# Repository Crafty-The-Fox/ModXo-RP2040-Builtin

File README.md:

# ModXo-RP2040-Included-Edition

A carrier board for the ModXo V1.0 with added support for Epimetheus. Based off of Darkone83's work. (reversed from gerbers and provided documents on the github page)

NOTE: anything after this is from the other repo.

This is designed around Team Resutgent's and Shalx's work on ModXo an open-source modchip, with additional support for OfficialTeamUIX's Epimetheus incorporated into the PCB

Mouser Cart: <a href="https://www.mouser.com/ProjectManager/ProjectDetail.aspx?AccessID=a62729557a">Here</a>

RP2040 Tiny: <a href="https://www.aliexpress.us/item/3256805837992528.html?spm=a2g0o.productlist.main.21.2f7926c5zGZBOW&algo_pvid=a59806cb-1f8b-4000-8595-0b05ca9fd6e6&algo_exp_id=a59806cb-1f8b-4000-8595-0b05ca9fd6e6-10&pdp_npi=4%40dis%21USD%217.22%214.48%21%21%217.22%214.48%21%402101c80217323295821625728e786b%2112000035369681956%21sea%21US%21196794698%21X&curPageLogUid=5ESoEvR4Kxce&utparam-url=scene%3Asearch%7Cquery_from%3A">AliExpress</a>, <a href="https://www.amazon.com/gp/product/B0CHDW1MY5/ref=ppx_yo_dt_b_asin_title_o02_s00?ie=UTF8&psc=1">Amazon</a>

JST SH 6 Pin Cables: 

<a href="https://www.aliexpress.us/item/3256804332710255.html?spm=a2g0o.detail.pcDetailTopMoreOtherSeller.5.245bNc4KNc4Kdm&gps-id=pcDetailTopMoreOtherSeller&scm=1007.40050.354490.0&scm_id=1007.40050.354490.0&scm-url=1007.40050.354490.0&pvid=6b58b5af-718a-4929-bfb1-9a0c24fd9d3c&_t=gps-id:pcDetailTopMoreOtherSeller,scm-url:1007.40050.354490.0,pvid:6b58b5af-718a-4929-bfb1-9a0c24fd9d3c,tpp_buckets:668%232846%238112%231997&pdp_npi=4%40dis%21USD%210.46%210.40%21%21%210.46%210.40%21%402103241117302619299196939e5dfc%2112000029449896682%21rec%21US%21196794698%21X&utparam-url=scene%3ApcDetailTopMoreOtherSeller%7Cquery_from%3A">AliExpress</a> Select 100mm length, 6 Pin 10 Pcs, SH 1.0MM Dual for Color, Request same direction!!!

Or if you want to build out your own you can use this listing on <a href="https://www.amazon.com/gp/product/B0BKSNMCV4/ref=ppx_yo_dt_b_asin_title_o03_s00?ie=UTF8&psc=1">Amazon</a>

For more information on the software side of things and the ModXo project please visit: https://github.com/Team-Resurgent/Modxo

For more information on Epimetheus please visit: https://github.com/OfficialTeamUIX/Epimetheus 

### Notice

No firmware is provided for the STM32 you will need to either code your own firmware or legally obtain a firmware image

#### Builder's note

If your XBOX is a revision 1.6 you will need to rebuild the LPC manually or use a LPC rebuild PCB.

# Purchase

Fully assembled boards and PCB's can be purchased via <a href="https://darkonecustoms.com">Darkone Customs</a>

PCB Only: <a href="https://www.darkonecustoms.com/store/p/modxo-epimetheus-pcb">Here</a>

Fully Assembled Board: <a href="https://www.darkonecustoms.com/store/p/modxo-epimetheus-fully-assembled">Here</a> *Fully assembled boards do not contain any firmware for the STM32*

# Navigation

Both the Bom and iBOMS are located in the root folder. iBOMS are included for the full-size board and the new Smol revision, Large board has been moved to archive

Archive: Will contain older functional gerbers and pick and place files as the board revs, along with older board images and older iBOMS.

Images: Contains branding images along with PCB images for the full-size and the Smol board, the schematic is also included here and is the same for both boards along with images of the various header pinouts and soldering locations

Smol: Contains gerbers for the Smol board along with the pick-and-place file

# Assembly

### ModXo

It's recommended to assemble the ModXo potion of the board first and test it. These parts include U1, D1, LED2, R1-4, R6, and the LPC headder. After functionality has been confirmed move on to the VCC circuit assembly

### VCC circuit

The VCC Circuit pulls 5V and GND from the LPC 5V on the 5V pad and GND can be found on PINs 2,12. The VCC circuit consists of the following parts U5, L1, C1-C2. After assembly, you can test PIN 5 of U5 to ensure a stable 3.3V output. Once you have confirmed you have 3.3V continue to assemble the STM32 circuit

### STM32

The STM32F030C8C6 is the core of the Epimetheus functionality portion of the board these components include U2. R7-10, C3-C6. Do not install R9 until you have programmed your STM32. Once assembly is complete you can proceed to program your STM32 Review the NRST Harness diagram and temporarily install it for programming. The NRST wire will connect to the top pad of R9 (the one closest to the MCU) and the GND side to any viable GND source. Remove the NRST harness once you have verified and tested your firmware. Install R9 to complete the STM32 circuit. SDA is pulled directly from PIN 13 of the LPC header and SCL is pulled directly from PIN 14. Pinouts will be listed below. Proceed to Port assembly

#### STM32 PWR and Enable
Attach a +5V source to the 5V pad on the topside of the board. On the back of the board jumper, both boxes are labeled enable with a solder blob. This was designed this way to assist in isolating the STM32 and the ModXo. As a quick tap, you can pull +5V from the bottom of LED2. 

### Port Assembly

Install U3, DISP, i2c_EXP, RGB_EXP, if using the RGB_EXP port install the jumper wire from the tiny to the RGB TP to enable the functionality.

### Notice

Soldering in the header for PROG is optional as you can insert pins and lightly wedge them in place to program the chip, R5, R6, LED1, and LED2 are optional. LED2 needs to be installed reverse of what the silk screen has labeled

# Installation

## 1.0 - 1.4

Install your pin header, Run a short wire from any suitable D0 point to either ground or the D0 point on the ModXo-Basic. Plug-in your ModXo-Basic to the XBOX LPC port (after you have flashed your favorite firmware) and enjoy.

#### D0 Point options

## 1.6

Either install a LPC rebuild QSB or rebuild your LPC per the rebuild diagram below. Plug-in your ModXo-Basic to the XBOX LPC port (after you have flashed your favorite firmware) and enjoy.

#### 1.6 LPC rebuild

# Pinouts 

Xbox LPC

Prog: 

U3: 

RGB_EXP: 

i2c_EXP: 

DISP: 

NRST Harnes:

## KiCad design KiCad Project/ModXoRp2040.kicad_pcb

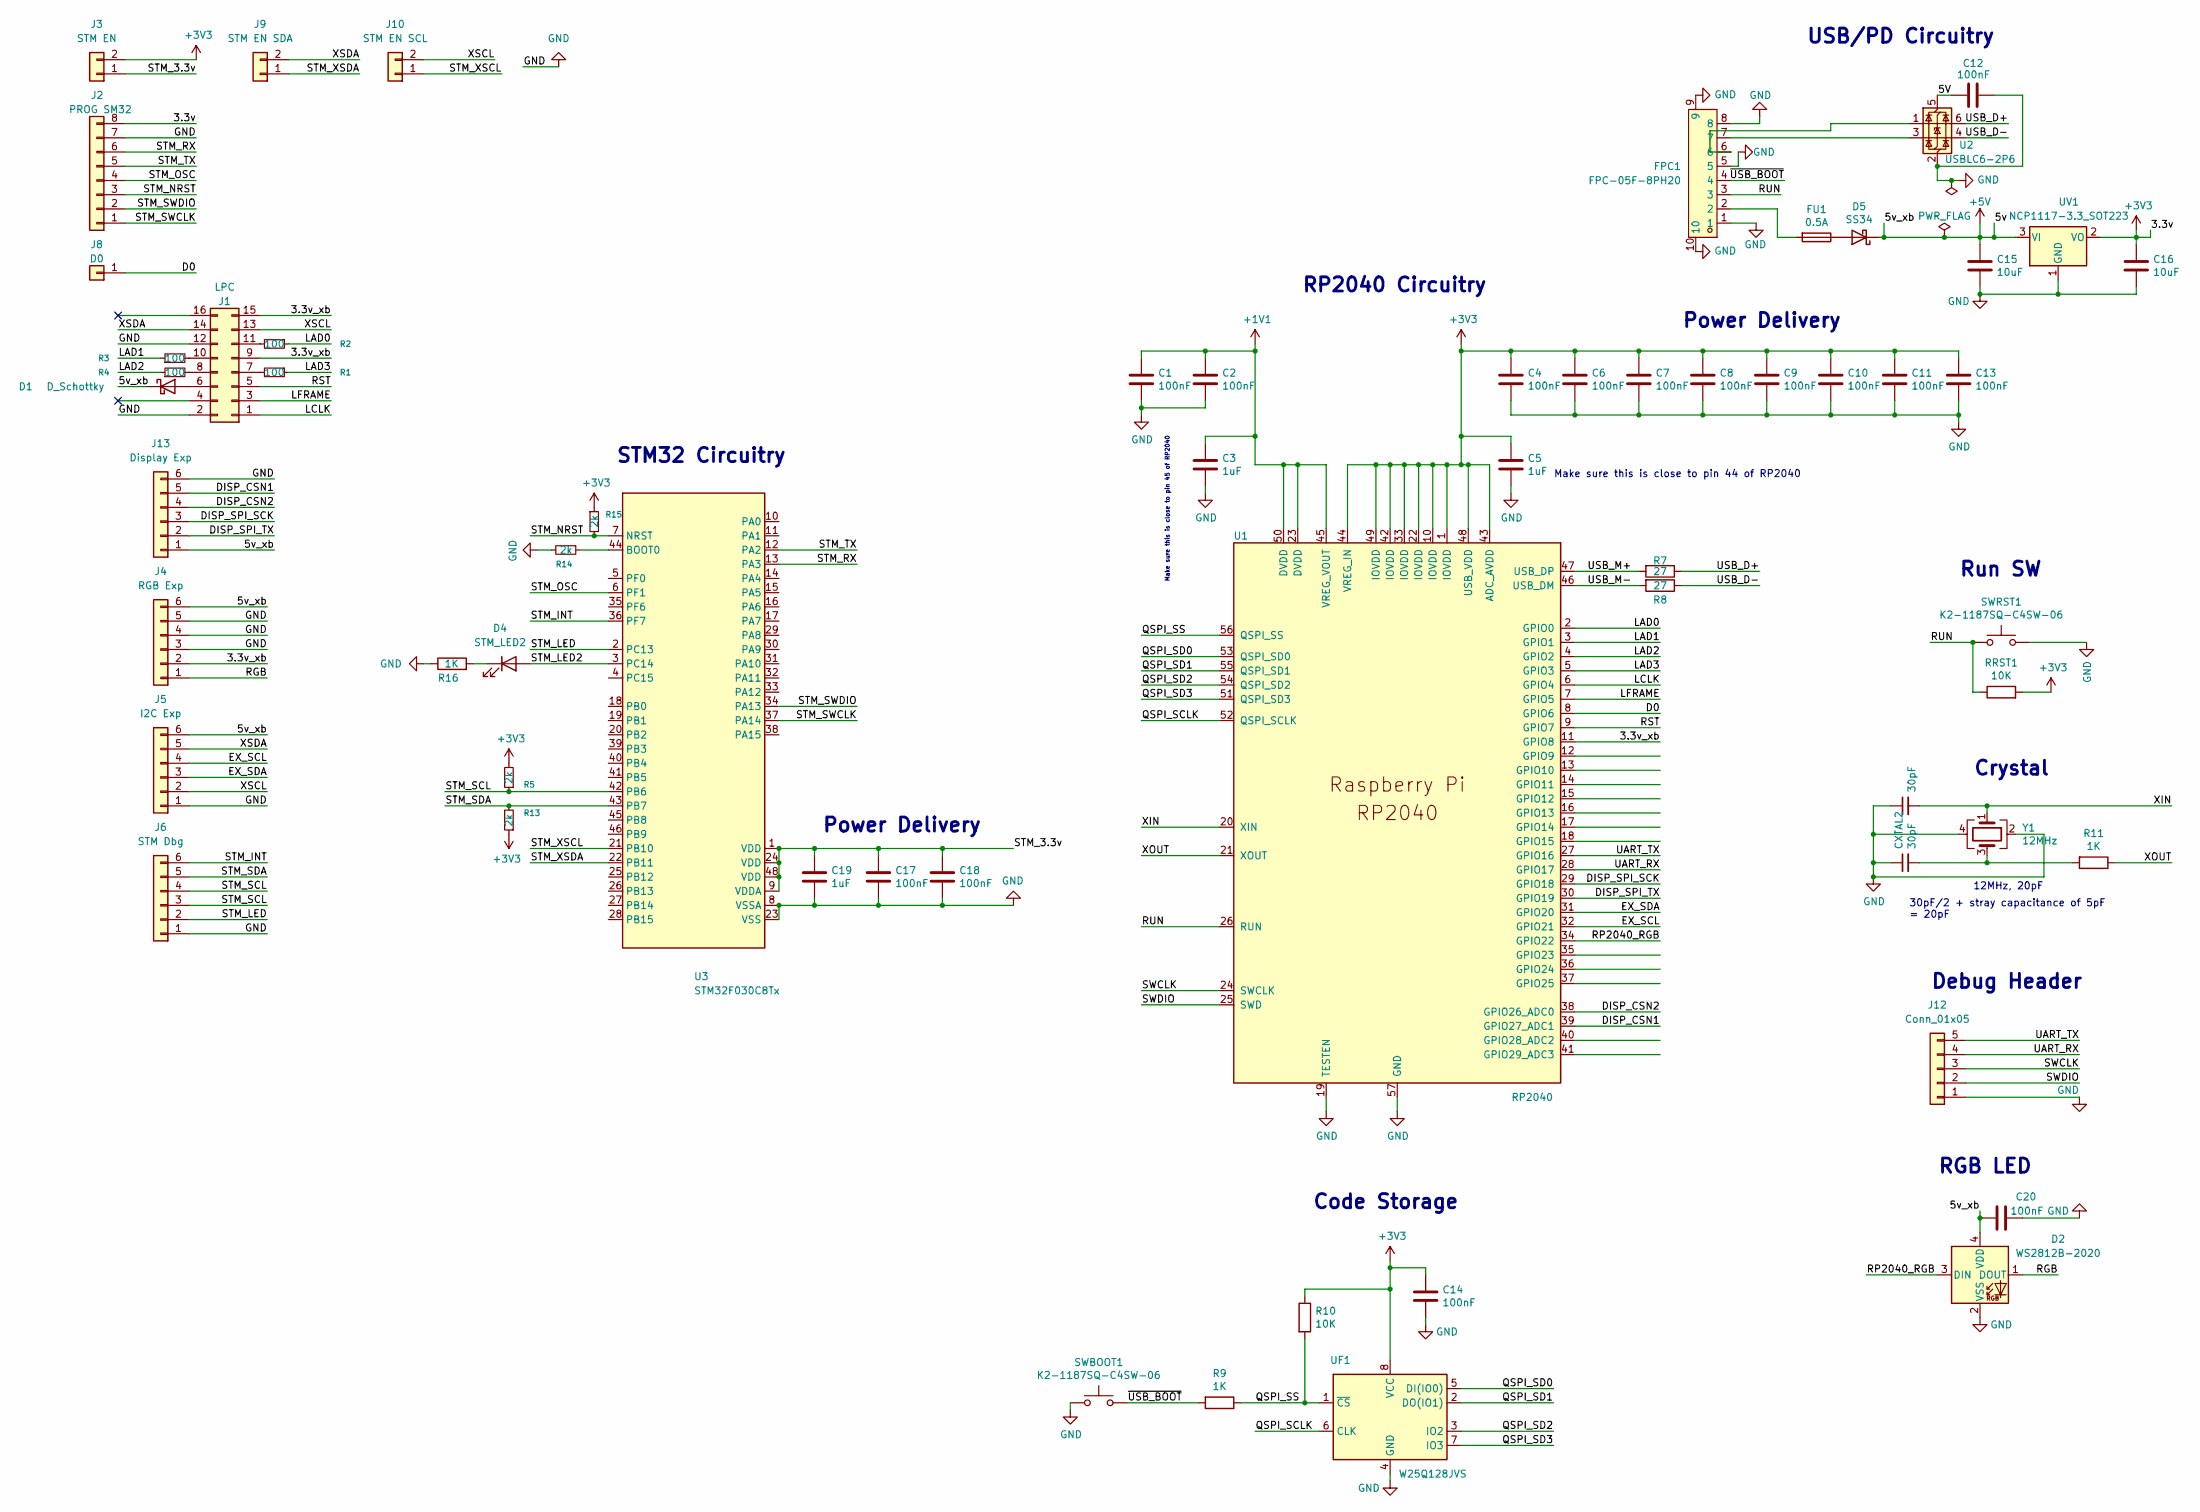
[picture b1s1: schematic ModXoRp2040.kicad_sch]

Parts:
C1, C2, C4, C6, C7, C8, C9, C10, C11, C12, C13, C14, C17, C18, C20: 100nF; C_0201_0603Metric; LCSC C1525
C3, C5, C19: 1uF; C_0201_0603Metric; LCSC C52923
C15, C16: 10uF; C_0201_0603Metric; LCSC C15850
CXTAL1, CXTAL2: 30pF; C_0201_0603Metric; LCSC C1570
D1: D_Schottky; D_SMA
D2: WS2812B-2020; LED_WS2812B-2020_PLCC4_2.0x2.0mm
D4: STM_LED2; LED_0402_1005Metric_Pad0.77x0.64mm_HandSolder; LCSC C165977
D5: SS34; D_SMA; LCSC C8678
FPC1: FPC-05F-8PH20; FPC-SMD_8P-P0.50_FPC-05F-8PH20; LCSC Part C2856797
FU1: 0.5A; Fuse_1206_3216Metric_Pad1.42x1.75mm_HandSolder; LCSC C70068
J1: LPC; PinSocket_2x08_P2.54mm_Vertical
J2: PROG SM32; PinSocket_1x08_P2.54mm_Vertical
J3: STM EN; SolderJumper-2_P1.3mm_Open_RoundedPad1.0x1.5mm
J4: RGB Exp; JST_SH_SM06B-SRSS-TB_1x06-1MP_P1.00mm_Horizontal
J5: I2C Exp; JST_SH_SM06B-SRSS-TB_1x06-1MP_P1.00mm_Horizontal
J6: STM Dbg; JST_SH_SM06B-SRSS-TB_1x06-1MP_P1.00mm_Horizontal
J8: D0; TestPoint_Pad_D1.5mm
J9: STM EN SDA; SolderJumper-2_P1.3mm_Open_RoundedPad1.0x1.5mm
J10: STM EN SCL; SolderJumper-2_P1.3mm_Open_RoundedPad1.0x1.5mm
J12: Conn_01x05; PinSocket_1x05_P2.00mm_Vertical
J13: Display Exp; JST_SH_SM06B-SRSS-TB_1x06-1MP_P1.00mm_Horizontal
R1, R2, R3, R4: 100; R_0201_0603Metric
R5, R13, R14, R15: 2k; R_0201_0603Metric
R7, R8: 27; R_0201_0603Metric; LCSC C25190
R9: 1K; R_0201_0603Metric; LCSC C21190
R10: 10K; R_0402_1005Metric; LCSC C25804
R11: 1K; R_0201_0603Metric; LCSC C11702
R16: 1K; R_0402_1005Metric; LCSC C21190
RRST1: 10K; R_0402_1005Metric; LCSC C25804
SWBOOT1: K2-1187SQ-C4SW-06; SolderJumper-2_P1.3mm_Open_RoundedPad1.0x1.5mm
SWRST1: K2-1187SQ-C4SW-06; SolderJumper-2_P1.3mm_Open_RoundedPad1.0x1.5mm
U1: RP2040; QFN-56-1EP_7x7mm_P0.4mm_EP3.2x3.2mm; LCSC C2040
U2: USBLC6-2P6; SOT-666
U3: STM32F030C8Tx; LQFP-48_7x7mm_P0.5mm
UF1: W25Q128JVS; SOIC-8_5.275x5.275mm_P1.27mm; LCSC C97521
UV1: NCP1117-3.3_SOT223; SOT-223-3_TabPin2; LCSC C146799
Y1: 12MHz; Crystal_SMD_3225-4Pin_3.2x2.5mm; LCSC C9002

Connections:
+1V1: C1.1, C2.1, C3.1, U1.23 (DVDD), U1.45 (VREG_VOUT), U1.50 (DVDD)
+3V3: C4.1, C5.1, C6.1, C7.1, C8.1, C9.1, C10.1, C11.1, C13.1, C14.1, C16.1, J2.8, J3.2, R5.2, R10.1, R13.1, R15.1, RRST1.2, U1.1 (IOVDD), U1.10 (IOVDD), U1.22 (IOVDD), U1.33 (IOVDD), U1.42 (IOVDD), U1.43 (ADC_AVDD), U1.44 (VREG_IN), U1.48 (USB_VDD), U1.49 (IOVDD), UF1.8 (VCC), UV1.2 (VO)
+5V: C15.1, C20.1, D1.1 (K), D2.4 (VDD), D5.1 (K), J4.6, J5.6, J13.1, UV1.3 (VI)
/3.3v_xb: J1.9, J1.15, J4.2, U1.11 (GPIO8)
/5V: C12.2, U2.5 (VBUS)
/D0: J8.1, U1.8 (GPIO6)
/DISP_CSN1: J13.5, U1.39 (GPIO27_ADC1)
/DISP_CSN2: J13.4, U1.38 (GPIO26_ADC0)
/DISP_SPI_SCK: J13.3, U1.29 (GPIO18)
/DISP_SPI_TX: J13.2, U1.30 (GPIO19)
/EX_SCL: J5.4, U1.32 (GPIO21)
/EX_SDA: J5.3, U1.31 (GPIO20)
/LAD0: R2.1, U1.2 (GPIO0)
/LAD1: R3.1, U1.3 (GPIO1)
/LAD2: R4.1, U1.4 (GPIO2)
/LAD3: R1.1, U1.5 (GPIO3)
/LCLK: J1.1, U1.6 (GPIO4)
/LFRAME: J1.3, U1.7 (GPIO5)
/QSPI_SCLK: U1.52 (QSPI_SCLK), UF1.6 (CLK)
/QSPI_SD0: U1.53 (QSPI_SD0), UF1.5 (DI(IO0))
/QSPI_SD1: U1.55 (QSPI_SD1), UF1.2 (DO(IO1))
/QSPI_SD2: U1.54 (QSPI_SD2), UF1.3 (IO2)
/QSPI_SD3: U1.51 (QSPI_SD3), UF1.7 (IO3)
/QSPI_SS: R9.1, R10.2, U1.56 (QSPI_SS), UF1.1 (~CS)
/RGB: D2.1 (DOUT), J4.1
/RP2040_RGB: D2.3 (DIN), U1.34 (GPIO22)
/RST: J1.5, U1.9 (GPIO7)
/RUN: FPC1.3, RRST1.1, SWRST1.1, U1.26 (RUN)
/STM_3.3v: C17.1, C18.1, C19.1, J3.1, U3.1 (VDD), U3.9 (VDDA), U3.24 (VDD), U3.48 (VDD)
/STM_INT: J6.6, U3.36 (PF7)
/STM_LED: J6.2, U3.2 (PC13)
/STM_LED2: D4.2 (A), U3.3 (PC14)
/STM_NRST: J2.3, R15.2, U3.7 (NRST)
/STM_OSC: J2.4, U3.6 (PF1)
/STM_RX: J2.6, U3.13 (PA3)
/STM_SCL: J6.3, J6.4, R5.1, U3.42 (PB6)
/STM_SDA: J6.5, R13.2, U3.43 (PB7)
/STM_SWCLK: J2.1, U3.37 (PA14)
/STM_SWDIO: J2.2, U3.34 (PA13)
/STM_TX: J2.5, U3.12 (PA2)
/STM_XSCL: J10.1, U3.21 (PB10)
/STM_XSDA: J9.1, U3.22 (PB11)
/SWCLK: J12.3, U1.24 (SWCLK)
/SWDIO: J12.2, U1.25 (SWD)
/UART_RX: J12.4, U1.28 (GPIO17)
/UART_TX: J12.5, U1.27 (GPIO16)
/USB_D+: R7.1, U2.6 (I/O1)
/USB_D-: R8.1, U2.4 (I/O2)
/USB_M+: R7.2, U1.47 (USB_DP)
/USB_M-: R8.2, U1.46 (USB_DM)
/XIN: CXTAL1.2, U1.20 (XIN), Y1.1
/XOUT: R11.1, U1.21 (XOUT)
/XSCL: J1.13, J5.2, J10.2
/XSDA: J1.14, J5.5, J9.2
/~USB_BOOT: FPC1.4, R9.2, SWBOOT1.2
GND: C1.2, C2.2, C3.2, C4.2, C5.2, C6.2, C7.2, C8.2, C9.2, C10.2, C11.2, C12.1, C13.2, C14.2, C15.2, C16.2, C17.2, C18.2, C19.2, C20.2, CXTAL1.1, CXTAL2.1, D2.2 (VSS), FPC1.1, FPC1.5, FPC1.8, FPC1.9, FPC1.10, J1.2, J1.12, J2.7, J4.3, J4.4, J4.5, J5.1, J6.1, J12.1, J13.6, R14.2, R16.1, SWBOOT1.1, SWRST1.2, U1.19 (TESTEN), U1.57 (GND), U2.2 (GND), U3.8 (VSSA), U3.23 (VSS), UF1.4 (GND), UV1.1 (GND), Y1.2, Y1.4
unnamed: CXTAL2.2, R11.2, Y1.3
unnamed: D1.2 (A), J1.6
unnamed: D4.1 (K), R16.2
unnamed: D5.2 (A), FU1.1
unnamed: FPC1.2, FU1.2
unnamed: FPC1.6, U2.1 (I/O1)
unnamed: FPC1.7, U2.3 (I/O2)
unnamed: J1.7, R1.2
unnamed: J1.8, R4.2
unnamed: J1.10, R3.2
unnamed: J1.11, R2.2
unnamed: R14.1, U3.44 (BOOT0)

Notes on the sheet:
Power Delivery
RP2040 Circuitry
Make sure this is close to pin 45 of RP2040
Make sure this is close to pin 44 of RP2040
12MHz, 20pF
Run SW
STM32 Circuitry
30pF/2 + stray capacitance of 5pF = 20pF
USB/PD Circuitry
RGB LED
Code Storage
Debug Header
Crystal

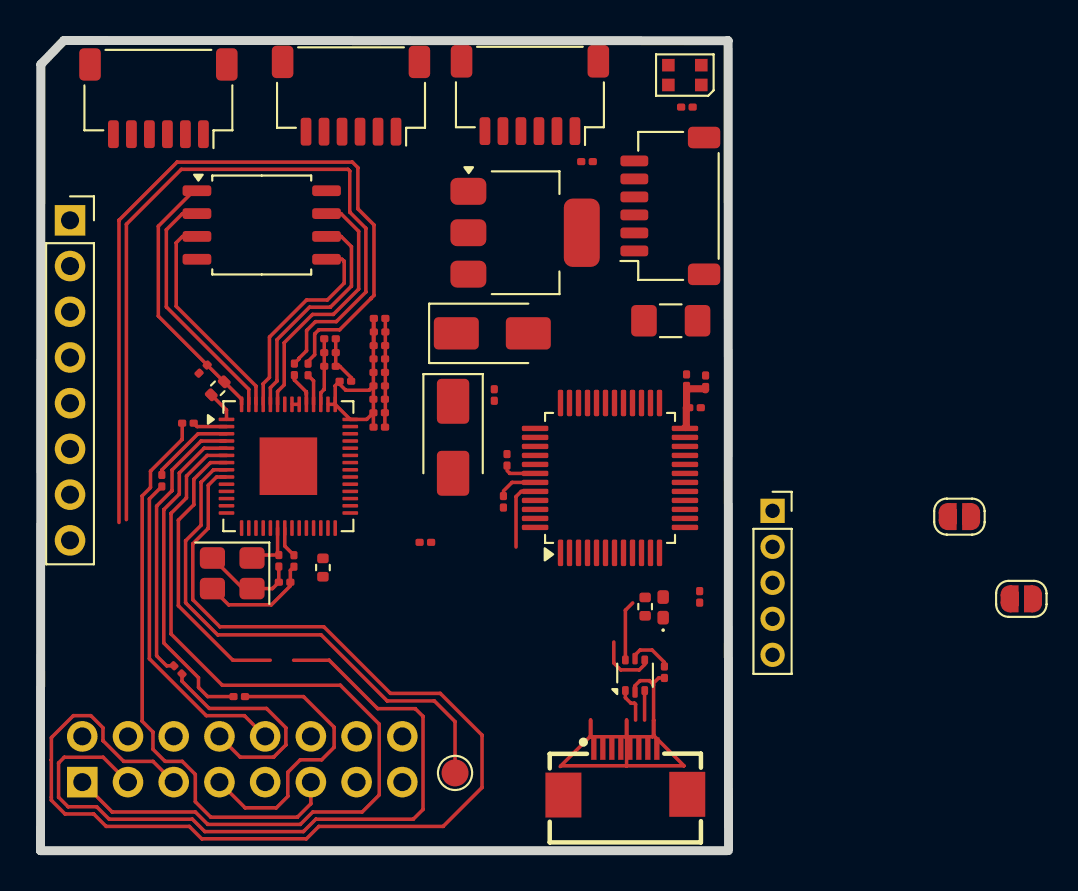
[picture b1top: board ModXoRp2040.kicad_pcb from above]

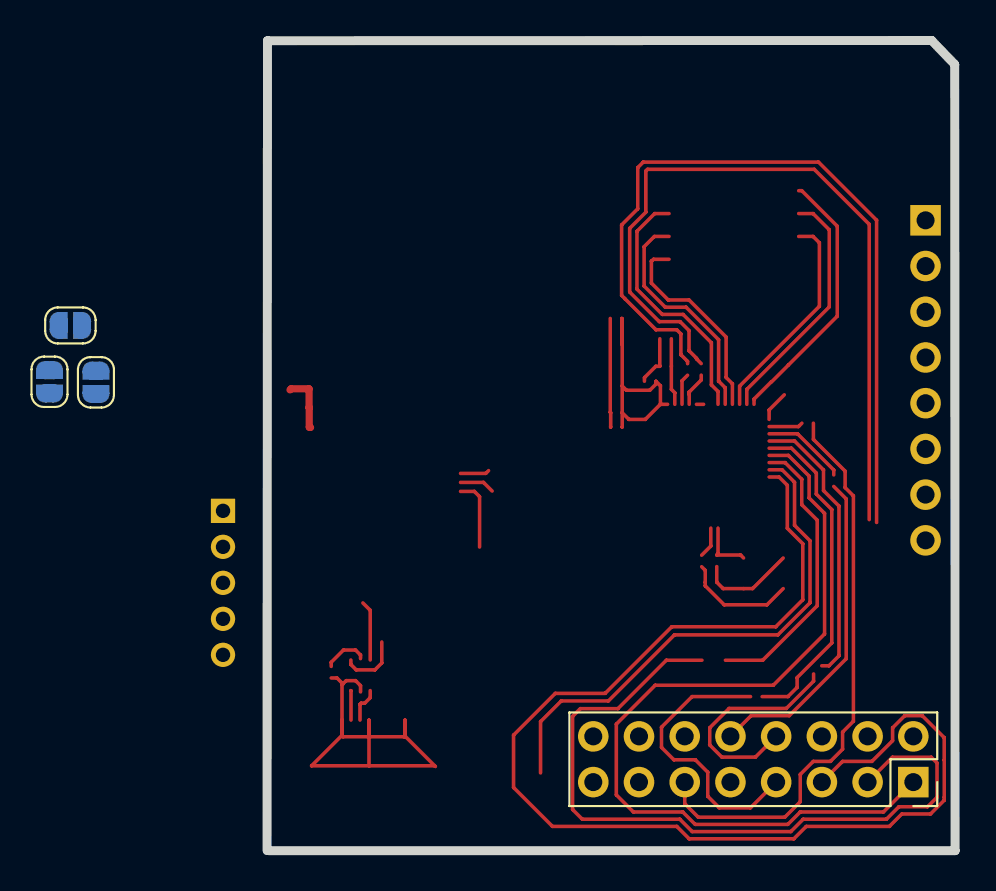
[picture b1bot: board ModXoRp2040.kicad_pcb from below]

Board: 2 copper layers, 38.2 x 45.0 mm, 62 parts (4 on the bottom side), 68 nets.

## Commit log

2025-12-01 crap i messed some stuff up when moving it
2025-12-01 added some stuff back
2025-12-01 update readme with reverse eng note
2025-12-01 oops i had a bunch of stuff messed up, whatever
2025-12-01 start pcb layout
2025-12-01 add .zip to gitignore to ignore autosaves
2025-12-02 finish schematics, start on pcb layout
2025-12-03 continue layout, put some tracks down
    need to rotate rp2040 otherwise layout is pretty much final?
2025-12-04 semi update
